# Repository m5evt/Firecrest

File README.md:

# Firecrest
This project is a dual band band HF CW transceiver design with a focus on portable operating. The design is realised across 3 stacked PCBs and the receiver is very similar to the N7VE/Norcal NC2030 and the transmitter PA is very similar to the KD1JV series of MTR rigs. This is not a kit, I intend to write a set of instruction to allow someone else with the appropriate skills to source their own components and build this radio.

Further information is on the [wiki](https://github.com/m5evt/Firecrest/wiki/).

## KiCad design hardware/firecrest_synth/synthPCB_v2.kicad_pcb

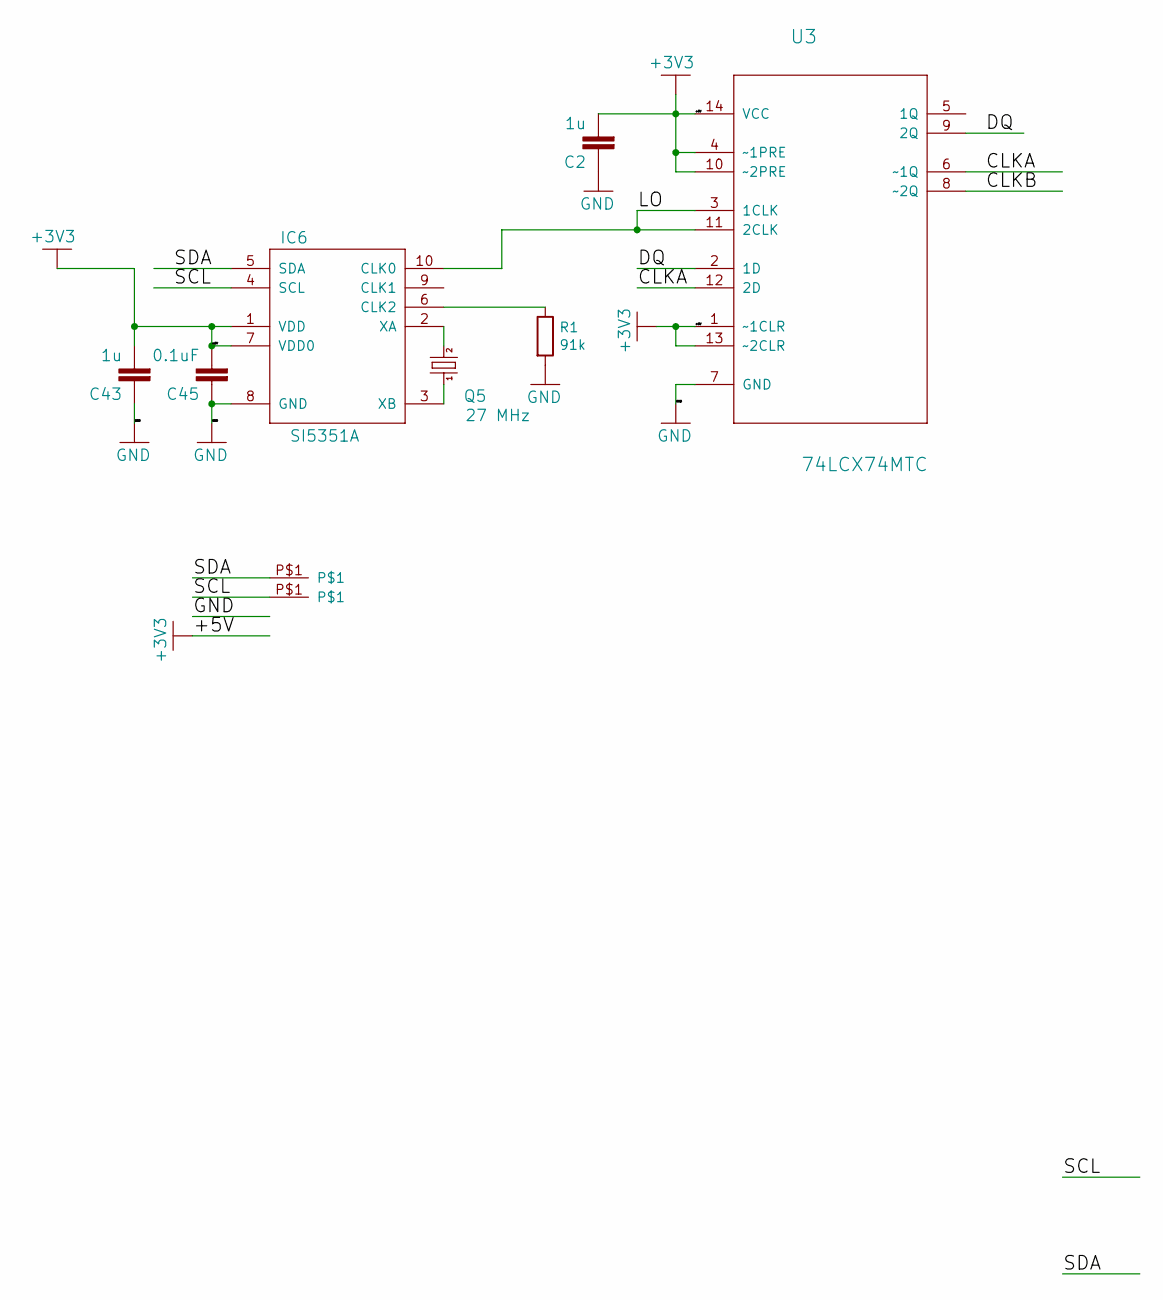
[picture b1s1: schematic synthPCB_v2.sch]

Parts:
C2, C43: 1u; C0603K
C45: 0.1uF; C0603K
IC6: SI5351A; MSOP10
Q5: 27 MHz; CTS406
R1: 91k; R_0603_1608Metric_Pad0.98x0.95mm_HandSolder
U3: 74LCX74MTC; SOP65P640X120-14N
U$5, U$6: EDGEPAD

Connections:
+5V: C2.2, C43.2, C45.2, IC6.1 (VDD), IC6.7 (VDD0), U3.1 (~~1CLR), U3.4 (~~1PRE), U3.10 (~~2PRE), U3.13 (~~2CLR), U3.14 (VCC)
/CLKA: U3.6 (~~1Q), U3.12 (2D)
/CLKB: U3.8 (~~2Q)
/DQ: U3.2 (1D), U3.9 (2Q)
/LO: IC6.10 (CLK0), U3.3 (1CLK), U3.11 (2CLK)
/SCL: IC6.4 (SCL), U$6.P$1
/SDA: IC6.5 (SDA), U$5.P$1
GND: C2.1, C43.1, C45.1, IC6.8 (GND), R1.2, U3.7 (GND)
unnamed: IC6.2 (XA), Q5.3 (2)
unnamed: IC6.3 (XB), Q5.1
unnamed: IC6.6 (CLK2), R1.1

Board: 2 copper layers, 13 parts (0 on the bottom side), 10 nets.

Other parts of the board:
@HOLE0, @HOLE1, @HOLE2, @HOLE3: (no value)

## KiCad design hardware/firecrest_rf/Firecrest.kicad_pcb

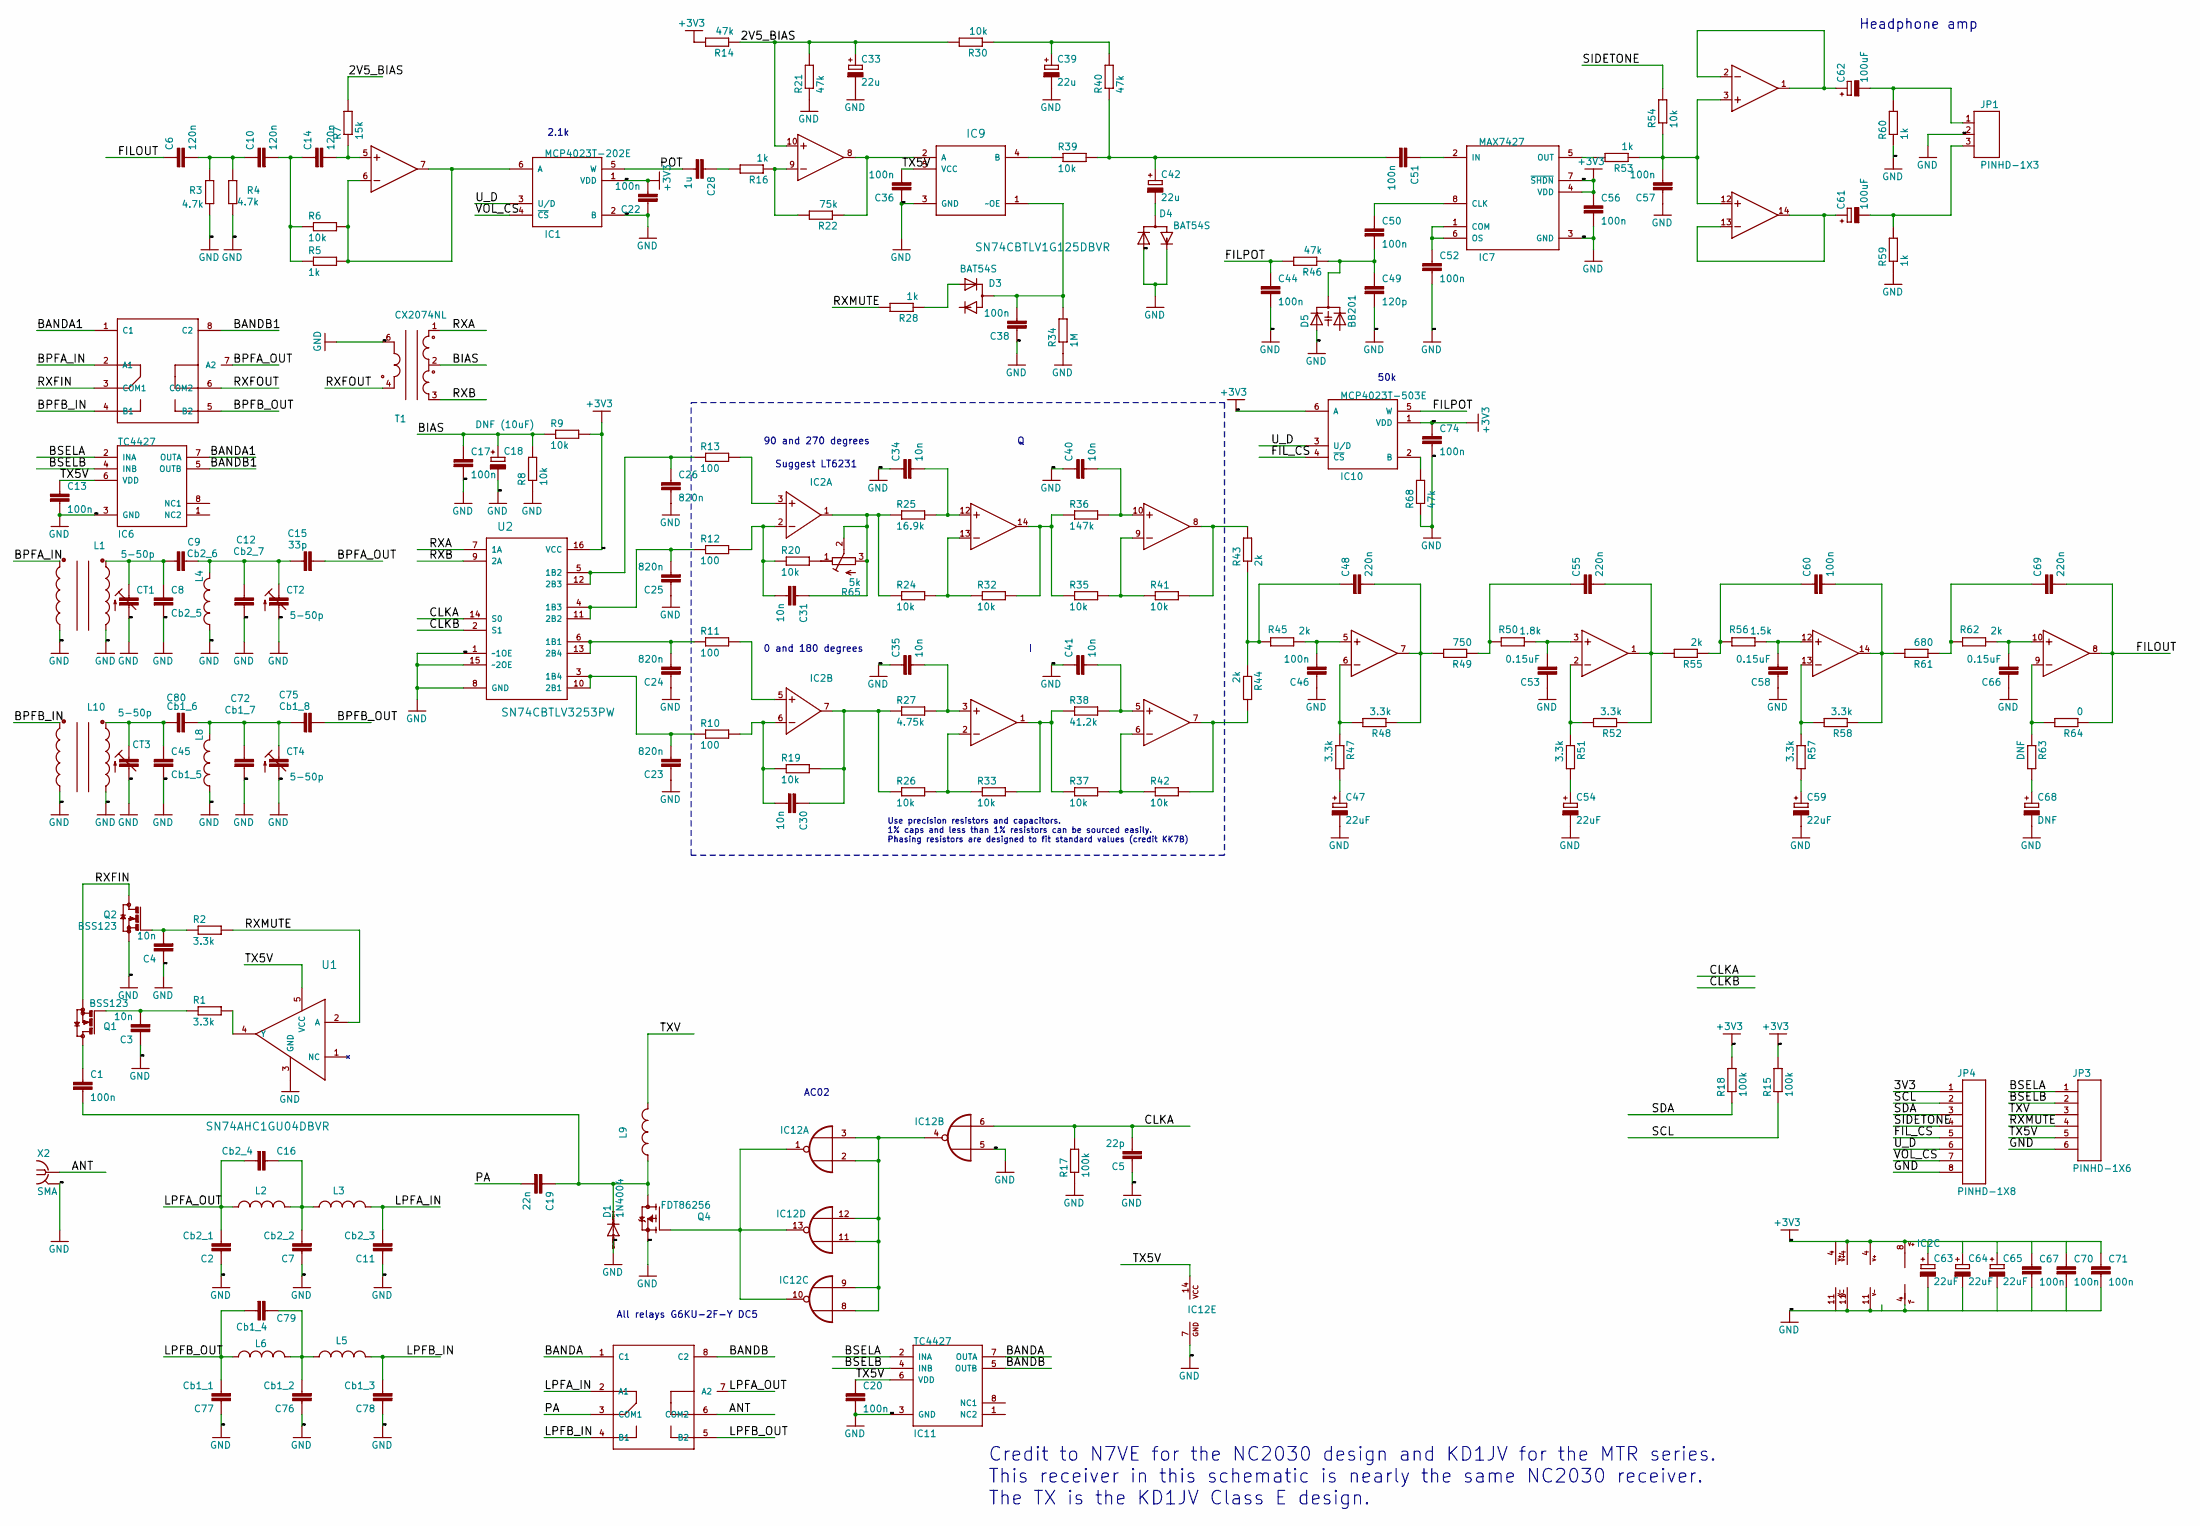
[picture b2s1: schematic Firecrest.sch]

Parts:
C1: 100n; C0805K
C2: Cb2_1; C0805K
C3, C4, C30, C31, C34, C35, C40, C41: 10n; C0603K
C5: 22p; C0603K
C6, C10, C14: 120n; C0603K
C7: Cb2_2; C0805K
C8: Cb2_5; C0603K
C9: Cb2_6; C0603K
C11: Cb2_3; C0805K
C12: Cb2_7; C0603K
C13, C17, C20, C22, C36, C38, C44, C46, C50, C51, C52, C56, C57, C60, C67, C70, C71, C74: 100n; C0603K
C15: 33p; C0603K
C16: Cb2_4; C0805K
C18: DNF (10uF); SMC_B
C19: 22n; C0805K
C23, C24, C25, C26: 820n; C0603K
C28: 1u; C0603K
C33, C39, C42: 22u; SMC_B
C45: Cb1_5; C0603K
C47, C54, C59, C63, C64, C65: 22uF; SMC_B
C48, C55, C69: 220n; C0603K
C49: 120p; C0603K
C53, C58, C66: 0.15uF; C0603K
C61, C62: 100uF; SMC_B
C68: DNF; SMC_B
C72: Cb1_7; C0603K
C75: Cb1_8; C0603K
C76: Cb1_2; C0805K
C77: Cb1_1; C0805K
C78: Cb1_3; C0805K
C79: Cb1_4; C0805K
C80: Cb1_6; C0603K
CT1, CT2, CT3, CT4: 5-50p; MURATA_TRIM
D1: 1N4004; DO41-10
D3, D4: BAT54S; SOT23
D5: BB201; SOT23
IC1: MCP4023T-202E; SOT23-6
IC2: LT6231; S8
IC4, IC5, IC8: TLV2464AID; SO14
IC6, IC11: TC4427; MSOP8
IC7: MAX7427; MSOP8
IC9: SN74CBTLV1G125DBVR; SOT95P280X145-5N
IC10: MCP4023T-503E; SOT23-6
IC12: 7402D; SO14
JP1: PINHD-1X3; 1X03
JP3: PINHD-1X6; 1X06
JP4: PINHD-1X8; 1X08
K1, K2: G6KU_OMRON
L1, L10: T30; T37_TRANSFORMER
L2, L3, L4, L6, L8: T30; T37_INDUCTOR
L5: T37; T37_INDUCTOR
L9: T37-43; T37_INDUCTOR
Q1, Q2: BSS123; SOT23
Q4: FDT86256; SOT223
R1, R2, R47, R48, R51, R52, R57, R58: 3.3k; R0603
R3, R4: 4.7k; R0603
R5, R16, R28, R53, R59, R60: 1k; R0603
R6, R8, R9, R19, R20, R24, R26, R30, R32, R33, R35, R37, R39, R41, R42, R54: 10k; R0603
R7: 15k; R0603
R10, R11, R12, R13: 100; R0603
R14, R21, R40, R46, R68: 47k; R0603
R15, R17, R18: 100k; R0603
R22: 75k; R0603
R25: 16.9k; R0603
R27: 4.75k; R0603
R34: 1M; R0603
R36: 147k; R0603
R38: 41.2k; R0603
R43, R44, R45, R55, R62: 2k; R0603
R49: 750; R0603
R50: 1.8k; R0603
R56: 1.5k; R0603
R61: 680; R0603
R63: DNF; R0603
R64: 0; R0603
R65: 5k; BOURNS3306W
T1: CX2074NL
U1: SN74AHC1GU04DBVR; SOT95P280X145-5N
U2: SN74CBTLV3253PW; SOP65P640X120-16N
X2: SMA; J502-ND-142-0701-801_806

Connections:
+5V: C22.2, C56.1, C63.+, C64.+, C65.+, C67.1, C70.1, C71.1, C74.1, IC1.1 (VDD), IC2.8 (V+), IC4.4 (V+), IC5.4 (V+), IC7.4 (VDD), IC7.7 (~SHDN), IC8.4 (V+), IC10.1 (VDD), IC10.6 (A), JP4.1, R9.2, R14.2, R15.2, R18.2, U2.16 (VCC)
/2V5_BIAS: C33.+, IC8.10 (+IN), R7.2, R14.1, R21.2, R30.2
/ANT: K2.6 (COM2), X2.1
/BANDA: IC11.7 (OUTA), K2.1 (C1)
/BANDA1: IC6.7 (OUTA), K1.1 (C1)
/BANDB: IC11.5 (OUTB), K2.8 (C2)
/BANDB1: IC6.5 (OUTB), K1.8 (C2)
/BIAS: C17.1, C18.+, R8.2, R9.1, T1.2
/BPFA_IN: K1.2 (A1), L1.C2B
/BPFA_OUT: C15.2, K1.7 (A2)
/BPFB_IN: K1.4 (B1), L10.C2B
/BPFB_OUT: C75.2, K1.5 (B2)
/BSELA: IC6.2 (INA), IC11.2 (INA), JP3.1
/BSELB: IC6.4 (INB), IC11.4 (INB), JP3.2
/CLKA: C5.2, IC12.6 (I1), R17.2, U2.14 (S0)
/CLKB: U2.2 (S1)
/FILOUT: C6.1, C69.2, IC5.8 (OUT), R64.1
/FILPOT: C44.1, IC10.5 (W), R46.2
/FIL_CS: IC10.4 (~CS), JP4.5
/LPFA_IN: C11.2, K2.2 (A1), L3.CA
/LPFA_OUT: C2.2, C16.2, K2.7 (A2), L2.CB
/LPFB_IN: C78.2, K2.4 (B1), L5.CA
/LPFB_OUT: C77.2, C79.2, K2.5 (B2), L6.CB
/PA: C19.2, K2.3 (COM1)
/POT: C28.2, IC1.5 (W)
/RXA: T1.1, U2.7 (1A)
/RXB: T1.3, U2.9 (2A)
/RXFIN: K1.3 (COM1), Q1.2 (S), Q2.3 (D)
/RXFOUT: K1.6 (COM2), T1.4
/RXMUTE: JP3.4, R2.2, R28.2, U1.2 (A)
/SCL: JP4.2, R15.1
/SDA: JP4.3, R18.1
/SIDETONE: JP4.4, R54.2
/TX5V: C13.1, C20.1, C36.2, IC6.6 (VDD), IC9.5 (VCC), IC11.6 (VDD), IC12.14 (VCC), JP3.5, U1.5 (VCC)
/TXV: JP3.3, L9.CA
/U_D: IC1.3 (U/D), IC10.3 (U/D), JP4.6
/VOL_CS: IC1.4 (~CS), JP4.7
GND: C2.1, C3.1, C4.1, C5.1, C7.1, C8.2, C11.1, C12.2, C13.2, C17.2, C18.-, C20.2, C22.1, C23.1, C24.1, C25.1, C26.2, C33.-, C34.1, C35.1, C36.1, C38.1, C39.-, C40.1, C41.1, C44.2, C45.2, C46.1, C47.-, C49.2, C52.2, C53.1, C54.-, C56.2, C57.1, C58.1, C59.-, C63.-, C64.-, C65.-, C66.1, C67.2, C68.-, C70.2, C71.2, C72.2, C74.2, C76.1, C77.1, C78.1, CT1.P$1 (A), CT2.P$1 (A), CT3.P$1 (A), CT4.P$1 (A), D1.A, D4.1 (A1), D4.2 (C2), D5.1 (A1), IC1.2 (B), IC2.4 (V-), IC4.11 (V-), IC5.11 (V-), IC6.3 (GND), IC7.3 (GND), IC8.11 (V-), IC9.3 (GND), IC11.3 (GND), IC12.5 (I0), IC12.7 (GND), JP1.2, JP3.6, JP4.8, L1.C1A, L1.C2A, L4.CB, L8.CB, L10.C1A, L10.C2A, Q2.2 (S), Q4.3 (S), R3.1, R4.1, R8.1, R17.1, R21.1, R34.1, R59.1, R60.1, R68.1, T1.6, U1.3 (GND), U2.1 (~~1OE), U2.8 (GND), U2.15 (~~2OE), X2.G@1 (2), X2.G@2 (2), X2.G@3 (2), X2.G@4 (2)
unnamed: C1.1, Q1.3 (D)
unnamed: C1.2, C19.1, D1.C, L9.CB, Q4.2 (D), Q4.4 (D)
unnamed: C3.2, Q1.1 (G), R1.1
unnamed: C4.2, Q2.1 (G), R2.1
unnamed: C8.1, C9.1, CT1.P$2 (E), L1.C1B
unnamed: C6.2, C10.1, R3.2, R4.2
unnamed: C10.2, C14.1, R5.1, R6.1
unnamed: C9.2, C12.1, C15.1, CT2.P$2 (E), L4.CA
unnamed: C14.2, IC8.5 (+IN), R7.1
unnamed: C7.2, C16.1, L2.CA, L3.CB
unnamed: C23.2, R10.1, U2.3 (1B4), U2.10 (2B1)
unnamed: C24.2, R11.1, U2.6 (1B1), U2.13 (2B4)
unnamed: C25.2, R12.1, U2.4 (1B3), U2.11 (2B2)
unnamed: C26.1, R13.1, U2.5 (1B2), U2.12 (2B3)
unnamed: C28.1, R16.2
unnamed: C30.1, IC2.7 (OUT), R19.2, R26.1, R27.1
unnamed: C30.2, IC2.6 (-IN), R10.2, R19.1
unnamed: C31.1, IC2.1 (OUT), R24.1, R25.1, R65.2 (S), R65.3 (E)
unnamed: C31.2, IC2.2 (-IN), R12.2, R20.1
unnamed: C34.2, IC4.12 (+IN), R25.2
unnamed: C35.2, IC4.3 (+IN), R27.2
unnamed: C38.2, D3.3 (C1A2), IC9.1 (~~OE), R34.2
unnamed: C39.+, R30.1, R40.2
unnamed: C40.2, IC4.10 (+IN), R36.2
unnamed: C41.2, IC4.5 (+IN), R38.2
unnamed: C42.+, C51.2, R39.2, R40.1
unnamed: C42.-, D4.3 (C1A2)
unnamed: C45.1, C80.1, CT3.P$2 (E), L10.C1B
unnamed: C46.2, IC5.5 (+IN), R45.1
unnamed: C47.+, R47.2
unnamed: C48.1, R43.1, R44.1, R45.2
unnamed: C48.2, IC5.7 (OUT), R48.1, R49.2
unnamed: C49.1, C50.2, D5.3 (C), R46.1
unnamed: C50.1, IC7.8 (CLK)
unnamed: C51.1, IC7.2 (IN)
unnamed: C52.1, IC7.1 (COM), IC7.6 (OS)
unnamed: C53.2, IC5.3 (+IN), R50.1
unnamed: C54.+, R51.2
unnamed: C55.1, R49.1, R50.2
unnamed: C55.2, IC5.1 (OUT), R52.1, R55.2
unnamed: C57.2, IC8.3 (+IN), IC8.12 (+IN), R53.1, R54.1
unnamed: C58.2, IC5.12 (+IN), R56.1
unnamed: C59.+, R57.2
unnamed: C60.1, R55.1, R56.2
unnamed: C60.2, IC5.14 (OUT), R58.1, R61.2
unnamed: C61.+, IC8.13 (-IN), IC8.14 (OUT)
unnamed: C61.-, JP1.3, R59.2
unnamed: C62.+, IC8.1 (OUT), IC8.2 (-IN)
unnamed: C62.-, JP1.1, R60.2
unnamed: C66.2, IC5.10 (+IN), R62.1
unnamed: C68.+, R63.2
unnamed: C69.1, R61.1, R62.2
unnamed: C72.1, C75.1, C80.2, CT4.P$2 (E), L8.CA
unnamed: C76.2, C79.1, L5.CB, L6.CA
unnamed: D3.1 (A1), R28.1
unnamed: IC1.6 (A), IC8.6 (-IN), IC8.7 (OUT), R5.2, R6.2
unnamed: IC2.3 (+IN), R13.2
unnamed: IC2.5 (+IN), R11.2
unnamed: IC4.1 (OUT), R33.2, R37.1, R38.1
unnamed: IC4.2 (-IN), R26.2, R33.1
unnamed: IC4.6 (-IN), R37.2, R42.1
unnamed: IC4.7 (OUT), R42.2, R44.2
unnamed: IC4.8 (OUT), R41.2, R43.2
unnamed: IC4.9 (-IN), R35.2, R41.1
unnamed: IC4.13 (-IN), R24.2, R32.1
unnamed: IC4.14 (OUT), R32.2, R35.1, R36.1
unnamed: IC5.2 (-IN), R51.1, R52.2
unnamed: IC5.6 (-IN), R47.1, R48.2
unnamed: IC5.9 (-IN), R63.1, R64.2
unnamed: IC5.13 (-IN), R57.1, R58.2
unnamed: IC7.5 (OUT), R53.2
unnamed: IC8.8 (OUT), IC9.2 (A), R22.1
unnamed: IC8.9 (-IN), R16.1, R22.2
unnamed: IC9.4 (B), R39.1
unnamed: IC10.2 (B), R68.2
unnamed: IC12.1 (O), IC12.10 (O), IC12.13 (O), Q4.1 (G)
unnamed: IC12.2 (I0), IC12.3 (I1), IC12.4 (O), IC12.8 (I0), IC12.9 (I1), IC12.11 (I0), IC12.12 (I1)
unnamed: R1.2, U1.4 (Y)
unnamed: R20.2, R65.1 (A)

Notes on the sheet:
Headphone amp
90 and 270 degrees
0 and 180 degrees
2.1k
50k
AC02
Suggest LT6231
All relays G6KU-2F-Y DC5
Credit to N7VE for the NC2030 design and KD1JV for the MTR series. This receiver in this schematic is nearly the same NC2030 receiver. The TX is the KD1JV Class E design.
Use precision resistors and capacitors. 1% caps and less than 1% resistors can be sourced easily. Phasing resistors are designed to fit standard values (credit KK7B)

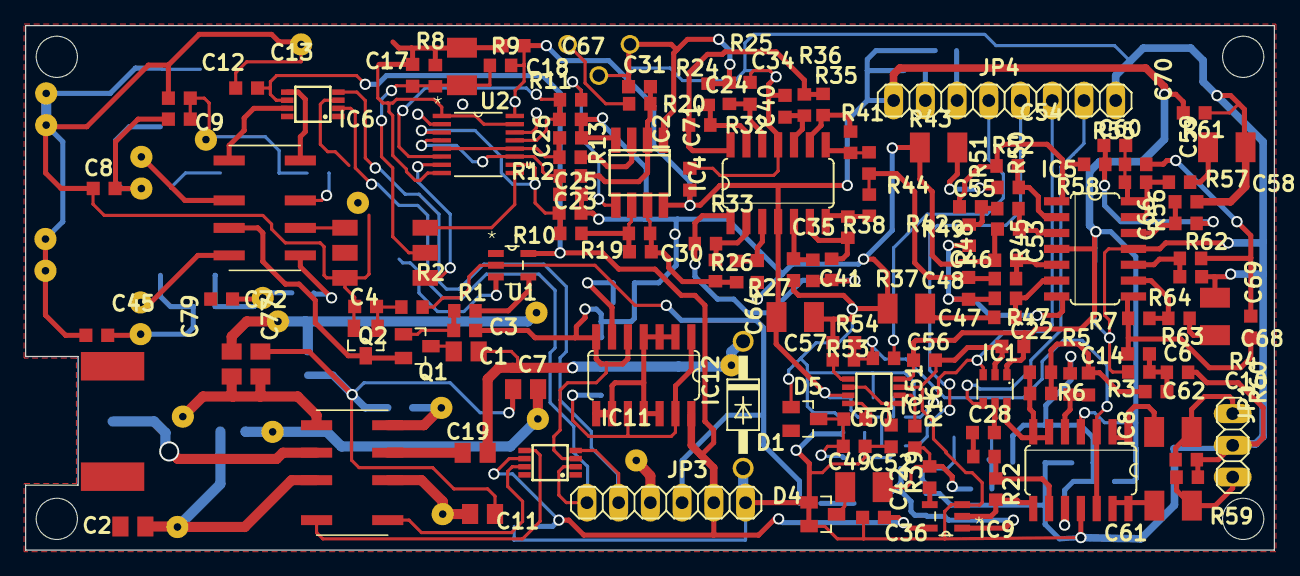
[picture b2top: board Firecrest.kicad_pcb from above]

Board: 2 copper layers, 100.0 x 42.0 mm, 180 parts (0 on the bottom side), 116 nets.

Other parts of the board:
@HOLE0, @HOLE1, @HOLE2, @HOLE3: (no value)

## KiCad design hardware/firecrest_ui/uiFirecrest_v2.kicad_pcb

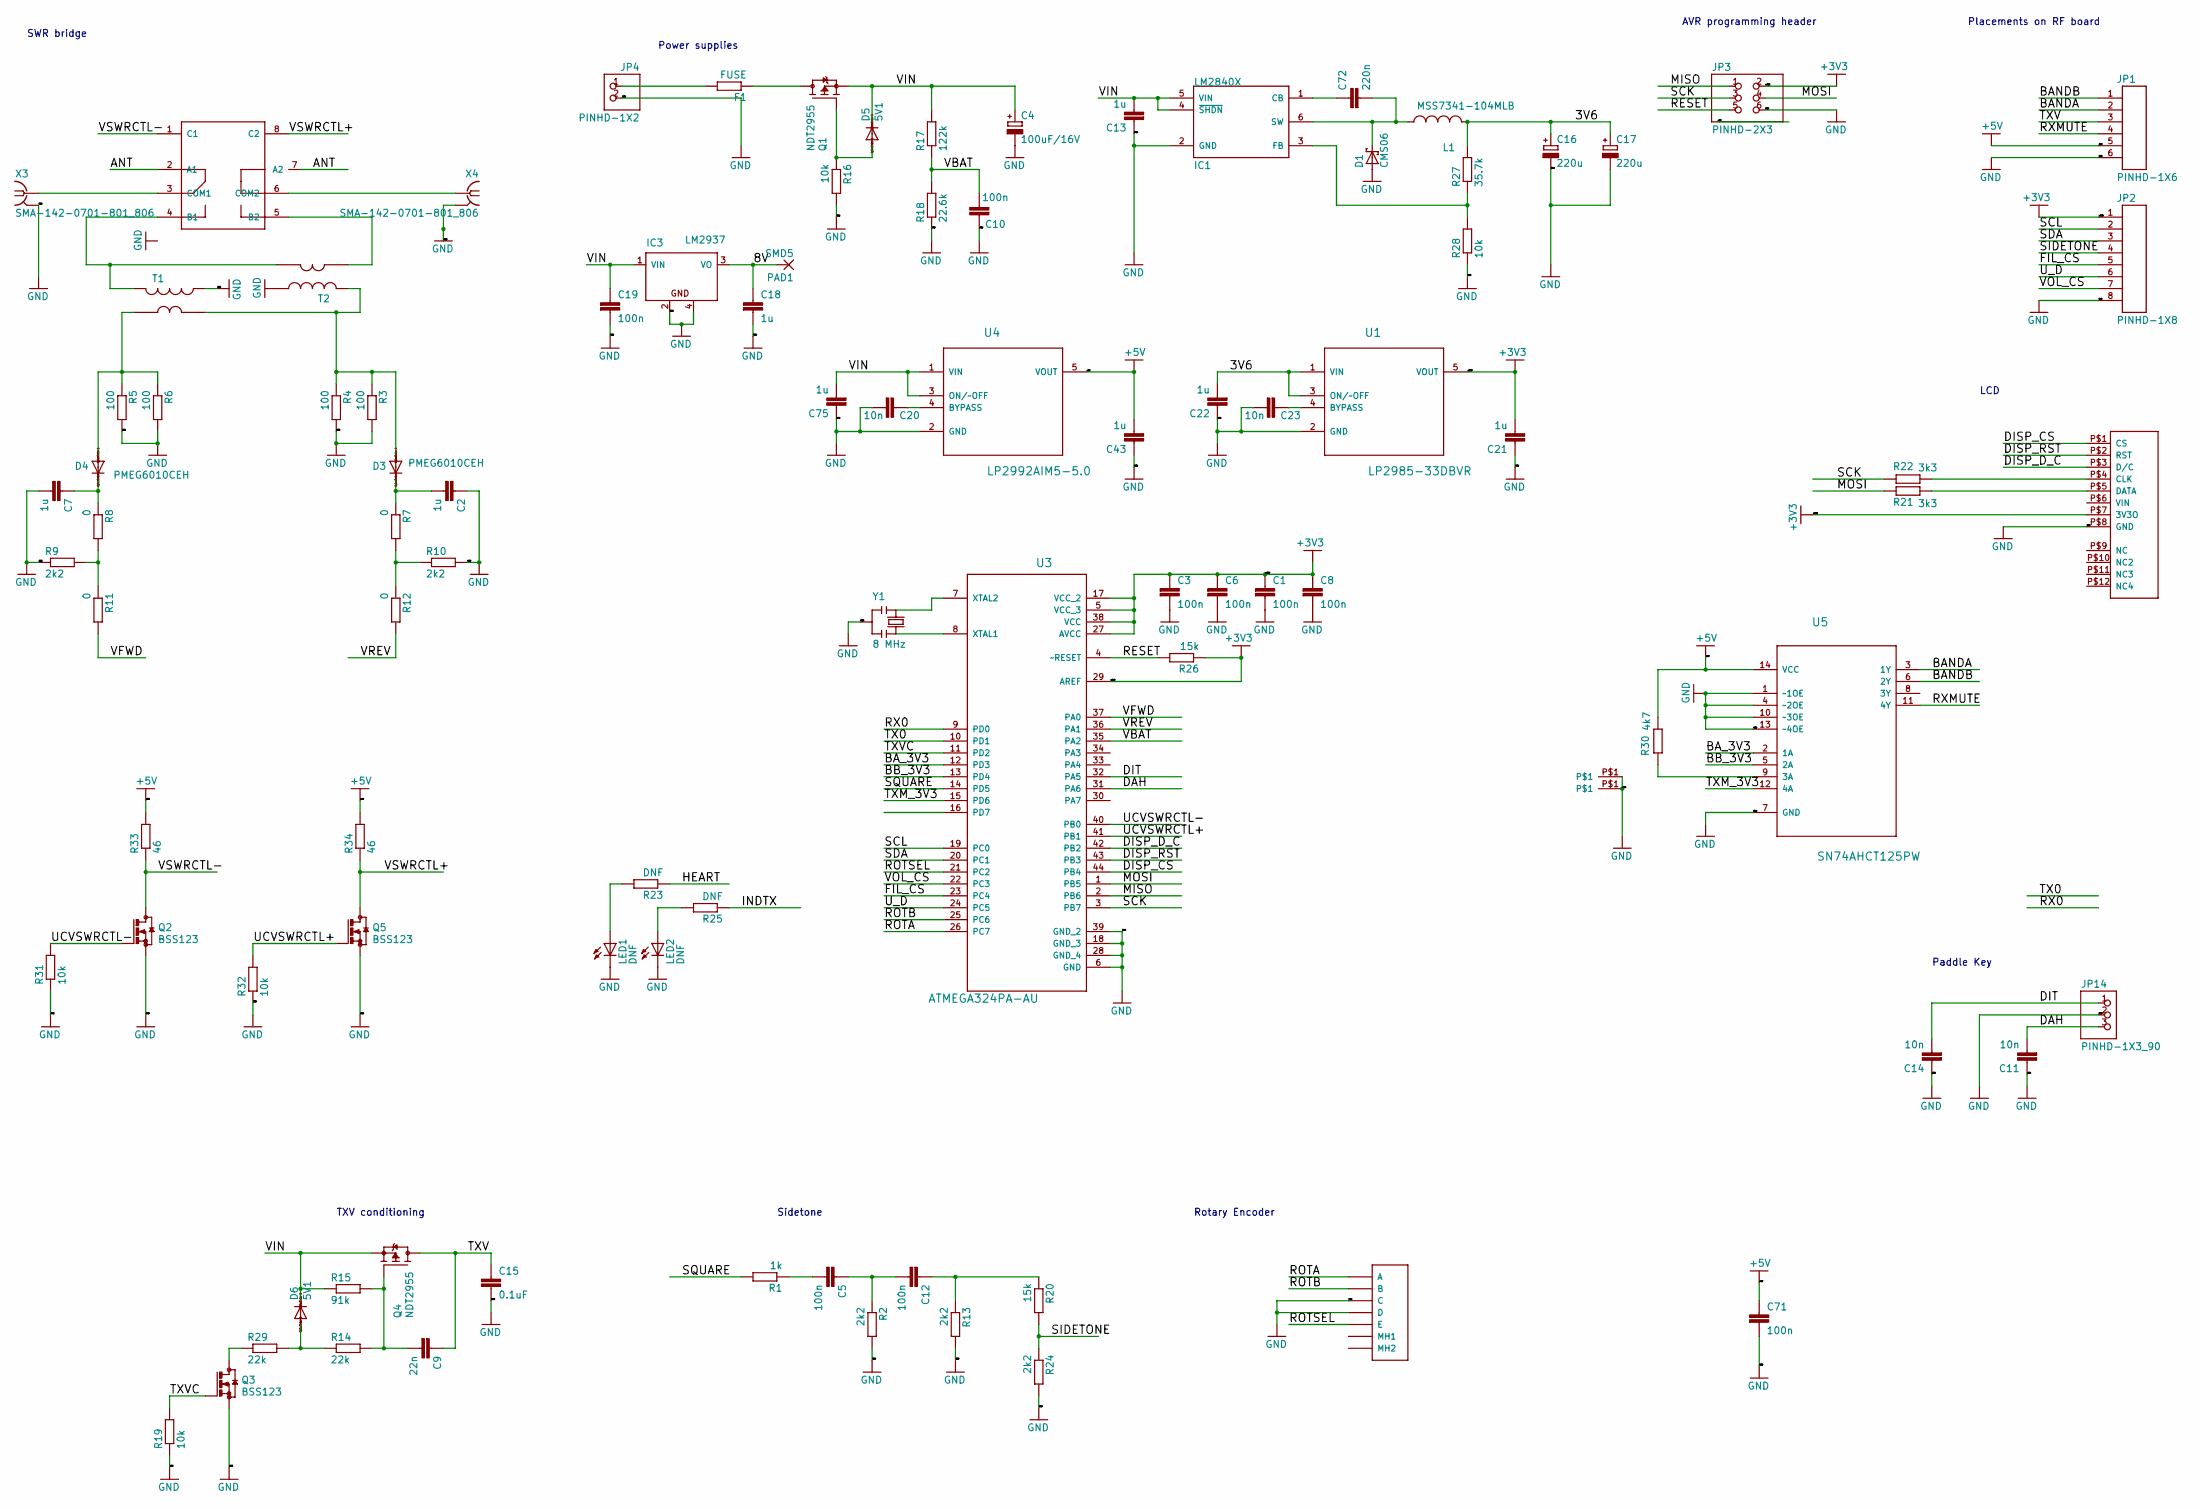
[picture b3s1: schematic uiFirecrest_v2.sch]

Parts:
C1, C3, C5, C6, C8, C10, C12, C71: 100n; C0603K
C2, C7, C13, C18, C43: 1u; C0805K
C4: 100uF/16V; SMC_D
C9: 22n; C0805K
C11, C14, C20, C23: 10n; C0603K
C15: 0.1uF; C0805K
C16, C17: 220u; SMC_D
C19: 100n; C0805K
C21, C22, C75: 1u; C0603K
C72: 220n; C0603K
D1: CMS06; CMS06_DIODE
D3, D4: PMEG6010CEH; SOD123
D5, D6: 5V1; SOD123
F1: FUSE; R1206W
IC1: LM2840X; SOT23-6
IC3: LM2937; SOT223
JP1: PINHD-1X6; 1X06
JP2: PINHD-1X8; 1X08
JP3: PINHD-2X3; 2X03
JP4: PINHD-1X2; 1X02
JP14: PINHD-1X3_90; 1X03_90
K1: G6KU_OMRON
L1: MSS7341-104MLB; LPS8045B-224MRB
LED1, LED2: DNF; SML0805
PAD1: SMD5; SMD2,54-5,08
Q1, Q4: NDT2955; SOT223
Q2, Q3, Q5: BSS123; SOT23
R1: 1k; R0603
R2, R9, R10, R13, R24: 2k2; R0603
R3, R4, R5, R6: 100; R0805
R7, R8: 0; R0603
R11, R12: 0; R0805
R14, R29: 22k; R0603
R15: 91k; R0603
R16, R19, R28, R31, R32: 10k; R0603
R17: 122k; R0603
R18: 22.6k; R0603
R20, R26: 15k; R0603
R21, R22: 3k3; R0603
R23, R25: DNF; R0603
R27: 35.7k; R0603
R30: 4k7; R0603
R33, R34: 46; R0603
T1, T2: T37-43; T37_THRU
U1: LP2985-33DBVR; SOT95P280X145-5N
U3: ATMEGA324PA-AU; QFP80P1200X1200X120-44N
U4: LP2992AIM5-5.0; SOT95P280X145-5N
U5: SN74AHCT125PW; SOP65P640X120-14N
U$1: OLED; OLED_LCD
U$2: ROTENC
U$3, U$4: RFCAN; CAN
X3, X4: SMA-142-0701-801_806; J502-ND-142-0701-801_806
Y1: 8 MHz; RESONATOR

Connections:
+3V3: C1.1, C3.1, C6.1, C8.1, C21.2, JP2.1, JP3.2, R26.1, U1.5 (VOUT), U3.5 (VCC_3), U3.17 (VCC_2), U3.27 (AVCC), U3.29 (AREF), U3.38 (VCC), U$1.P$7 (3V3O)
+5V: C43.2, C71.1, JP1.5, R30.1, R33.2, R34.2, U4.5 (VOUT), U5.14 (VCC)
/3V6: C16.+, C17.+, C22.2, L1.1 (CA), R27.2, U1.1 (VIN), U1.3 (ON/~~OFF)
/8V: C18.1, IC3.3 (VO), PAD1.1
/ANT: K1.2 (A1), K1.7 (A2)
/BANDA: JP1.2, U5.3 (1Y)
/BANDB: JP1.1, U5.6 (2Y)
/BA_3V3: U3.12 (PD3), U5.2 (1A)
/BB_3V3: U3.13 (PD4), U5.5 (2A)
/DAH: C11.2, JP14.3, U3.31 (PA6)
/DISP_CS: U3.44 (PB4), U$1.P$1 (CS)
/DISP_D_C: U3.42 (PB2), U$1.P$3 (D/C)
/DISP_RST: U3.43 (PB3), U$1.P$2 (RST)
/DIT: C14.2, JP14.1, U3.32 (PA5)
/FIL_CS: JP2.5, U3.23 (PC4)
/HEART: R23.1
/INDTX: R25.1
/MISO: JP3.1, U3.2 (PB6)
/MOSI: JP3.4, R21.2, U3.1 (PB5)
/RESET: JP3.5, R26.2, U3.4 (~~RESET)
/ROTA: U3.26 (PC7), U$2.P$1 (A)
/ROTB: U3.25 (PC6), U$2.P$2 (B)
/ROTSEL: U3.21 (PC2), U$2.P$5 (E)
/RX0: U3.9 (PD0)
/RXMUTE: JP1.4, U5.11 (4Y)
/SCK: JP3.3, R22.2, U3.3 (PB7)
/SCL: JP2.2, U3.19 (PC0)
/SDA: JP2.3, U3.20 (PC1)
/SIDETONE: JP2.4, R20.2, R24.1
/SQUARE: R1.2, U3.14 (PD5)
/TX0: U3.10 (PD1)
/TXM_3V3: U3.15 (PD6), U5.12 (4A)
/TXV: C9.1, C15.1, JP1.3, Q4.2 (D), Q4.4 (D)
/TXVC: Q3.1 (G), R19.2, U3.11 (PD2)
/UCVSWRCTL+: Q5.1 (G), R32.2, U3.41 (PB1)
/UCVSWRCTL-: Q2.1 (G), R31.2, U3.40 (PB0)
/U_D: JP2.6, U3.24 (PC5)
/VBAT: C10.2, R17.1, R18.2, U3.35 (PA2)
/VFWD: R11.2, U3.37 (PA0)
/VIN: C4.+, C13.2, C19.1, C75.2, D5.C, D6.C, IC1.4 (~SHDN), IC1.5 (VIN), IC3.1 (VIN), Q1.3 (S), Q4.3 (S), R15.1, R17.2, U4.1 (VIN), U4.3 (ON/~~OFF)
/VOL_CS: JP2.7, U3.22 (PC3)
/VREV: R12.2, U3.36 (PA1)
/VSWRCTL+: K1.8 (C2), Q5.3 (D), R34.1
/VSWRCTL-: K1.1 (C1), Q2.3 (D), R33.1
GND: C1.2, C2.1, C3.2, C4.-, C6.2, C7.2, C8.2, C10.1, C11.1, C13.1, C14.1, C15.2, C16.-, C17.-, C18.2, C19.2, C20.2, C21.1, C22.1, C23.2, C43.1, C71.2, C75.1, D1.AN (A), IC1.2 (GND), IC3.2 (GND@1), IC3.4 (GND@2), JP1.6, JP2.8, JP3.6, JP4.2, JP14.2, LED1.C, LED2.C, Q2.2 (S), Q3.2 (S), Q5.2 (S), R2.2, R3.2, R4.2, R5.2, R6.2, R9.1, R10.2, R13.2, R16.2, R18.1, R19.1, R24.2, R28.1, R31.1, R32.1, T1.C1B (BA), T2.C1B (BA), U1.2 (GND), U3.6 (GND), U3.18 (GND_3), U3.28 (GND_4), U3.39 (GND_2), U4.2 (GND), U5.1 (~~1OE), U5.4 (~~2OE), U5.7 (GND), U5.10 (~~3OE), U5.13 (~~4OE), U$1.P$8 (GND), U$2.P$3 (C), U$2.P$4 (D), U$3.P$1, U$4.P$1, X3.G@1 (2), X3.G@2 (2), X3.G@3 (2), X3.G@4 (2), X4.G@1 (2), X4.G@2 (2), X4.G@3 (2), X4.G@4 (2), Y1.2
unnamed: C2.2, D3.C, R7.1
unnamed: C5.2, R1.1
unnamed: C7.1, D4.C, R8.1
unnamed: C9.2, Q4.1 (G), R14.2, R15.2
unnamed: C12.1, R13.1, R20.1
unnamed: C5.1, C12.2, R2.1
unnamed: C20.1, U4.4 (BYPASS)
unnamed: C23.1, U1.4 (BYPASS)
unnamed: C72.1, IC1.1 (CB)
unnamed: C72.2, D1.CAT (C), IC1.6 (SW), L1.2 (CB)
unnamed: D3.A, R3.1, R4.1, T1.THRU1 (SA), T2.C2A (BB)
unnamed: D4.A, R5.1, R6.1, T1.THRU2 (SB)
unnamed: D5.A, Q1.1 (G), R16.1
unnamed: D6.A, R14.1, R29.2
unnamed: F1.1, Q1.2 (D), Q1.4 (D)
unnamed: F1.2, JP4.1
unnamed: IC1.3 (FB), R27.1, R28.2
unnamed: K1.3 (COM1), X3.1
unnamed: K1.4 (B1), T1.C2A (BB), T2.THRU1 (SA)
unnamed: K1.5 (B2), T2.THRU2 (SB)
unnamed: K1.6 (COM2), X4.1
unnamed: LED1.A, R23.2
unnamed: LED2.A, R25.2
unnamed: Q3.3 (D), R29.1
unnamed: R7.2, R10.1, R12.1
unnamed: R8.2, R9.2, R11.1
unnamed: R21.1, U$1.P$5 (DATA)
unnamed: R22.1, U$1.P$4 (CLK)
unnamed: R30.2, U5.9 (3A)
unnamed: U3.7 (XTAL2), Y1.1
unnamed: U3.8 (XTAL1), Y1.3

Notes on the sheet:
Placements on RF board
SWR bridge
LCD
Paddle Key
Power supplies
AVR programming header
TXV conditioning
Rotary Encoder
Sidetone

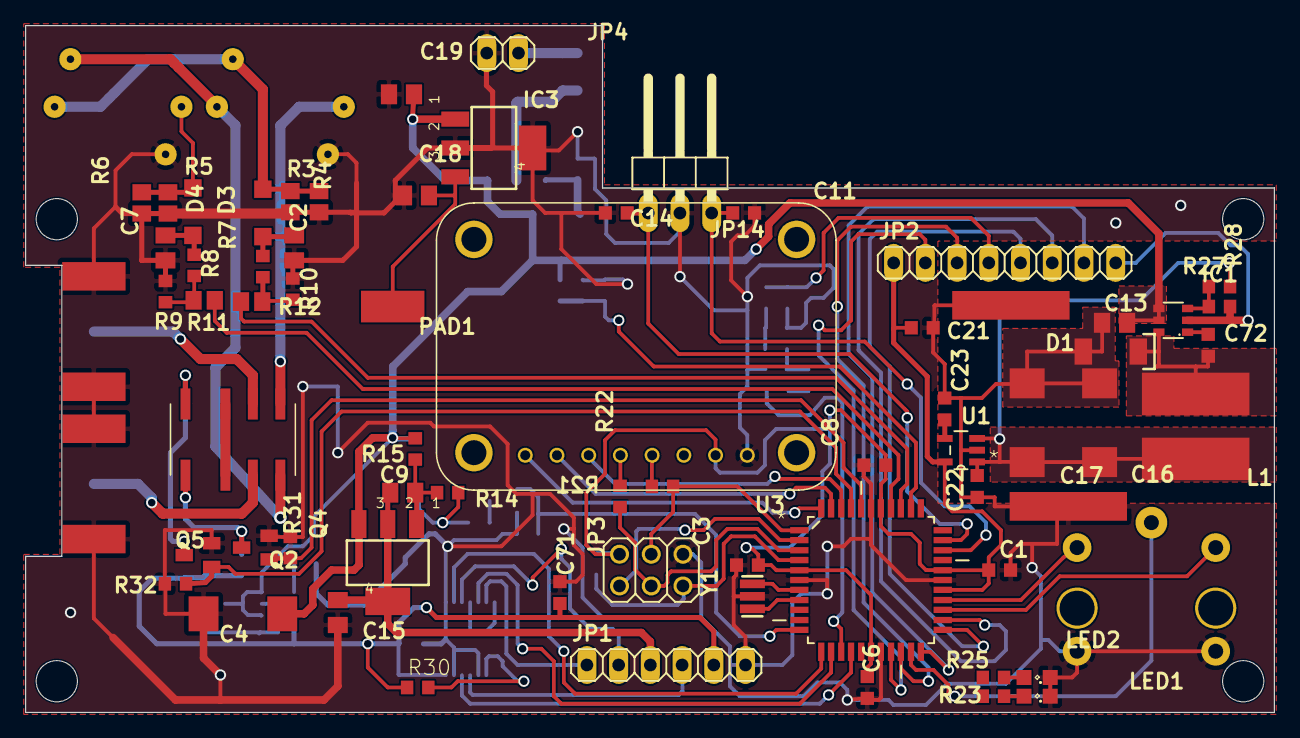
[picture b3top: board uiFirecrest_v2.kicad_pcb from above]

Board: 2 copper layers, 100.0 x 55.0 mm, 101 parts (0 on the bottom side), 72 nets.

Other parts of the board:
@HOLE0, @HOLE1, @HOLE2, @HOLE3: (no value)

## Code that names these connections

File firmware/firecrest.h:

/* 
 * Copyright 2021 m5evt
 * 
 * This is free software; you can redistribute it and/or modify
 * it under the terms of the GNU General Public License as published by
 * the Free Software Foundation; either version 3, or (at your option)
 * any later version.
 * 
 * This software is distributed in the hope that it will be useful,
 * but WITHOUT ANY WARRANTY; without even the implied warranty of
 * MERCHANTABILITY or FITNESS FOR A PARTICULAR PURPOSE.  See the
 * GNU General Public License for more details.
 * 
 * You should have received a copy of the GNU General Public License
 * along with this software; see the file COPYING.  If not, write to
 * the Free Software Foundation, Inc., 51 Franklin Street,
 * Boston, MA 02110-1301, USA.
 *
 */
 
#ifndef FIRECREST_H
#define FIRECREST_H

#include <avr/eeprom.h>
#include "helper.h"
#include "yack.h"
/*
#define vFWD		SBIT(PINA, 0) 
#define vREV 		SBIT(PINA, 1) 
#define vBAT 		SBIT(PINA, 2) 
#define txVTC		SBIT(PORTA, 3) 
#define txON		SBIT(PORTA, 4) 
#define dit 		SBIT(PORTA, 5) 
#define dah 		SBIT(PORTA, 6) 
#define rotSEL		SBIT(PINA, 7)

#define RFSWMINS	SBIT(PORTB, 0) 
#define RFSWPLUS	SBIT(PORTB, 1) 
#define indtxLED2	SBIT(PORTB, 2) 
#define heartLED1	SBIT(PORTB, 3) 
#define dispPWR		SBIT(PORTB, 4) 
//#define mosi		SBIT(PORTB, 5) 
//#define miso		SBIT(PORTB, 6) 
//#define sck		SBIT(PORTB, 7) 

//#define 			SBIT(PORTC, 0) 		// i2c
//#define 			SBIT(PORTC, 1)	// i2c 

#define VOLCS		SBIT(PORTC, 3) 
#define FILCS		SBIT(PORTC, 4) 
#define VOLUD		SBIT(PORTC, 5) 
#define rotB		SBIT(PINC, 6) 
#define rotA		SBIT(PINC, 7) 

//#define rx0		SBIT(PORTD, 0)
//#define tx0		SBIT(PORTD, 1)
#define uartPWR		SBIT(PORTD, 2)
//#define uartPWR	SBIT(PORTD, 3)	//Reserved
#define dispDC		SBIT(PORTD, 4)
#define dispRST		SBIT(PORTD, 5)
#define dispCS		SBIT(PORTD, 6)
//#define sidetone	SBIT(PORTD, 7)	// Reserved

*/

//********Yack
#define	KEYINP	PINA
#define KEYTX		SBIT(PORTD, 2) 
#define DITPIN	SBIT(PINA, 5) 								
#define DAHPIN	SBIT(PINA, 6) 
#define BTNPIN	SBIT(PINA, 7) 

//********Tx
#define rxMUTE SBIT(PORTD, 6)

//********General system settings
#define ROTA		SBIT(PINC, 7) 	//Rotary encoder B
#define ROTB		SBIT(PINC, 6) 	//Rotary encoder A
#define ROTSEL	SBIT(PINC, 2)	//Main push button

#define RFSWMINS	SBIT(PORTB, 0) 
#define RFSWPLUS	SBIT(PORTB, 1) 

#define VOLCS		SBIT(PORTC, 3) 
#define FILCS		SBIT(PORTC, 4) 
#define VOLUD		SBIT(PORTC, 5) 

#define BANDA		SBIT(PORTD, 3) 	
#define BANDB		SBIT(PORTD, 4) 	

#define STPIN		SBIT(PORTD, 5)

#define ddrPORTA	0b10011000
#define ddrPORTB	0b11111111
#define ddrPORTC	0b00111011
#define ddrPORTD	0b11111111

//OLED Defs
#define SSD1306_CS_PORT 	PORTB
#define SSD1306_CS_PIN		4
#define SSD1306_DC_PORT 	PORTB
#define SSD1306_DC_PIN		2
#define SSD1306_RST_PORT	PORTB
#define SSD1306_RST_PIN		3

#define SSD1306_SCLK_PORT 	PORTB
#define SSD1306_SCLK_PIN  	7
#define SSD1306_SDAT_PORT 	PORTB
#define SSD1306_SDAT_PIN  	5

#define NARROW	0
#define WIDE		1

#define BAND1		10
#define BAND2		14

#define BAND1_UPPER 	10150000
#define BAND1_LOWER		10100000
#define BAND1_F			  10118000

#define BAND2_UPPER	  14100000	
#define BAND2_LOWER   14000000	
#define BAND2_F			  14062000

// If changing this, must change timer in init micro
#define TXOFFSET  650

#define MAX_CALLSIGN_LEN 15

char callStr[15];

/*    
extern volatile unsigned int txKeyed = 0;    
extern uint8_t enableMemoryReplay = 0;		
extern uint8_t battery_state = 0;
extern volatile unsigned int txKeyed;
*/


#define		MAGPAT			0xA5    // If this number is found in EEPROM, content assumed valid

typedef struct {
	char e_call[MAX_CALLSIGN_LEN];
  uint8_t e_kmod;
  uint8_t e_kwpm;
  uint8_t e_filt;
  uint8_t e_band;
  uint8_t e_replay_time;
  uint16_t e_increment;
} eesave_t;

struct systemSettings {
	uint16_t increment;
	uint32_t freq;
	uint32_t ritFreq;
	uint32_t upperFreq;
	uint32_t lowerFreq;
	uint16_t volume;
	uint8_t filterMode;
	uint8_t autoReplay;
	uint8_t band;
	uint8_t keyMode;
};

struct menuStateMachine {
	uint8_t currentState;
	uint8_t txState;
	uint8_t pbCounterOn;
	uint8_t pbCounterOff;
};

enum menuStateDescript {
	Frequency,
	RIT,
	Vol,
	FSTEP,
	Tune,
	M1P,
	M1R,
	Wpm,
	KMOD,
	Fil,
	MAR,
	Band
};       

enum menuDetailsDescript {
    OffTest,
    On,
    Rec,
    Narrow,
    Wide,
    IA,
    IB,
    Str,
    Ul
};  

/*************************************************************************
//Function Prototypes
*************************************************************************/
extern uint16_t getVSWR(void);
extern void transistion_to_rx(void);
extern void transition_to_tx(void);
extern void service_vswr(void);
extern void disable_memory_replay(void);
#endif

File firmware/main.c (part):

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	uint16_t i = 0;
	
	KEYTX = 0;
	rxMUTE = 1;
  // Default callsign
  strcpy(callStr, "M5EVT/P");    

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	ssd1306Refresh();
	
	//Mute: 1 = mute, 0 = audio
  rxMUTE = 0;
	
	//Send call sign welcome CW
	yackinhibit(ON);  //side tone greeting to confirm the unit is alive
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          
          transition_to_tx();
          
          //rxMUTE = 1;
          //cli();
          //si5351_clock_enable(SI5351_CLK2, 1);					
          //sei();  
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        key(UP);
        transistion_to_rx();
        //txKeyed = 0;
        //rxMUTE = 0;
        //yackbeat();
        //cli();
        //si5351_clock_enable(SI5351_CLK2, 0);					
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			case  Vol: 		// 2
				{	
				if (inc == 1 && setting->volume != 9) {
					rxMUTE = 1;	
					volumeUPone();
					rxMUTE = 0;	
					setting->volume += 1;
				    clearMainArea();
				    drawIntNumber(setting->volume);	
				}
				else if (dec == 1 && setting->volume != 0) {
					rxMUTE = 1;
					volumeDOWNone();					
					rxMUTE = 0;	
					setting->volume -= 1;
					clearMainArea();
					drawIntNumber(setting->volume);						
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				{			
				if (inc == 1 || dec == 1) {
					if (setting->filterMode == WIDE) {
						rxMUTE = 1;	
						for (i=0;i<8;i++) {
							filterDOWNone();
						}	
						rxMUTE = 0;	
						setting->filterMode = NARROW;
					}
					else if (setting->filterMode == NARROW) {
						rxMUTE = 1;	
						for (i=0;i<8;i++) {
							filterUPone();
						}					
						rxMUTE = 0;	
						setting->filterMode = WIDE;
					}	
          save = 1;
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}

uint16_t getVSWR(void) {
	//Vrev PA0 ADC0 
	//Vfwd PA1 ADC1
	uint16_t measVfwd;
	uint16_t measVrev;
	
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}

static void serviceBattery(void) {
	//Get ADC value from PA2/ADC2
	//Check if it is less than low bat warning
  // if it is audible beep
	ADCSRA |= (1 << ADPS2) | (1 << ADPS1) | (1 << ADPS0); // Set ADC prescalar to 128 - 125KHz sample rate @ 16MHz 
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static void ChangeBand(uint8_t band, struct systemSettings *setting) {
	switch(band) {        
    case	BAND2: 	
      BANDA = 0;
			BANDB = 0;
			BANDA = 1;
			BANDB = 0;
			yackbeat();	
			BANDA = 0;
			BANDB = 0;
			setting->freq = ((BAND2_F + TXOFFSET) * 4);
			setting->ritFreq = ((BAND2_F + TXOFFSET) * 4);
			setting->upperFreq = ((BAND2_UPPER*4) + (TXOFFSET * 4));
			setting->lowerFreq = ((BAND2_LOWER*4) + (TXOFFSET * 4));			
			break;
    case	BAND1: 
      BANDA = 0;
			BANDB = 0;
			BANDA = 0;
			BANDB = 1;
			yackbeat();	
			BANDA = 0;
			BANDB = 0;
			setting->freq = ((BAND1_F + TXOFFSET) * 4);
			setting->ritFreq = ((BAND1_F + TXOFFSET) * 4);
      setting->upperFreq = ((BAND1_UPPER*4) + (TXOFFSET * 4));
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static void memoryCQ(void) {
	yackinhibit(OFF);
	
  //rxMUTE = 1;
	//cli();
	//si5351_clock_enable(SI5351_CLK2, 1);
	//sei();    
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	
	//yackinhibit(ON);
	//txKeyed = 0;
	//rxMUTE = 0;
	//cli();
	//si5351_clock_enable(SI5351_CLK2, 0);					
	//sei();	
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
void transistion_to_rx(void) {
  txKeyed = 0;
  rxMUTE = 0;
  cli();
  si5351_clock_enable(SI5351_CLK2, 0);					
  sei();
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
void transition_to_tx(void) {
  txKeyed = 1;  
  rxMUTE = 1;
  cli();
  si5351_clock_enable(SI5351_CLK2, 1);
  sei(); 
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
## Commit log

2020-07-13 Schematic
2021-01-03 kicad and firmware
2022-05-12 Bug fixes and code tidy up
2022-05-12 Save increment in eeprom
2022-05-12 Tidy up
